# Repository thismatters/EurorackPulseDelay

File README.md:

# Pulse Delay

The circuit here is based on the [Yusynth Pulse Delay](https://yusynth.net/Modular/EN/PULSEDELAY/index.html) with minor tweaks to make it more Eurorack friendly. The changes I've made are thus:
* Selected resistors appropriate for +/-12V rails,
* Added polarity protection so that a backward power header doesn't fry anything (twin series schotty diodes: BAT54SL),
* Full surface mount design.

The Yusynth page is a treasure trove of information about this circuit that I am too amateur to claim as my own; please read that outstanding page before using this circuit. The page provides many details and other implementations of this circuit that you may find suitable.

The KiCAD project here uses the library/footprints [found in my companion repo](https://github.com/thismatters/EurorackKiCAD).

## Width

13hp on an Intellijel 1U rack.

## Inputs

Jack for gate/pulse input.

Knobs for:
* Pulse delay
* Pulse width

## Outputs

Jack for gate/pulse output.

LED to indicate output.

## Vendors

There are part numbers in the [BOM](pulse-delay.csv) for many of the parts (not for basic passives though) at the following vendors:

* [Mouser](https://www.mouser.com): Needs no introduction. Get your ICs from here (or [digikey](https://www.digikey.com)).
* [Tayda Electronics](https://www.taydaelectronics.com/): Good supplier for passive components; audio jacks, and potentiometers. Their audio jacks are slightly smaller than the thonkiconn from thonk.
* [Love My Switches](https://lovemyswitches.com/): Has [really good knobs](https://lovemyswitches.com/anodized-aluminum-knob-the-lo-fi-1-4-smooth-shaft-12-5mm-od/) to go on those potentiometers!
* [OSHPark](https://oshpark.com/): Fast and (relatively) cheap PCB manufacturer. Prototype run pending.

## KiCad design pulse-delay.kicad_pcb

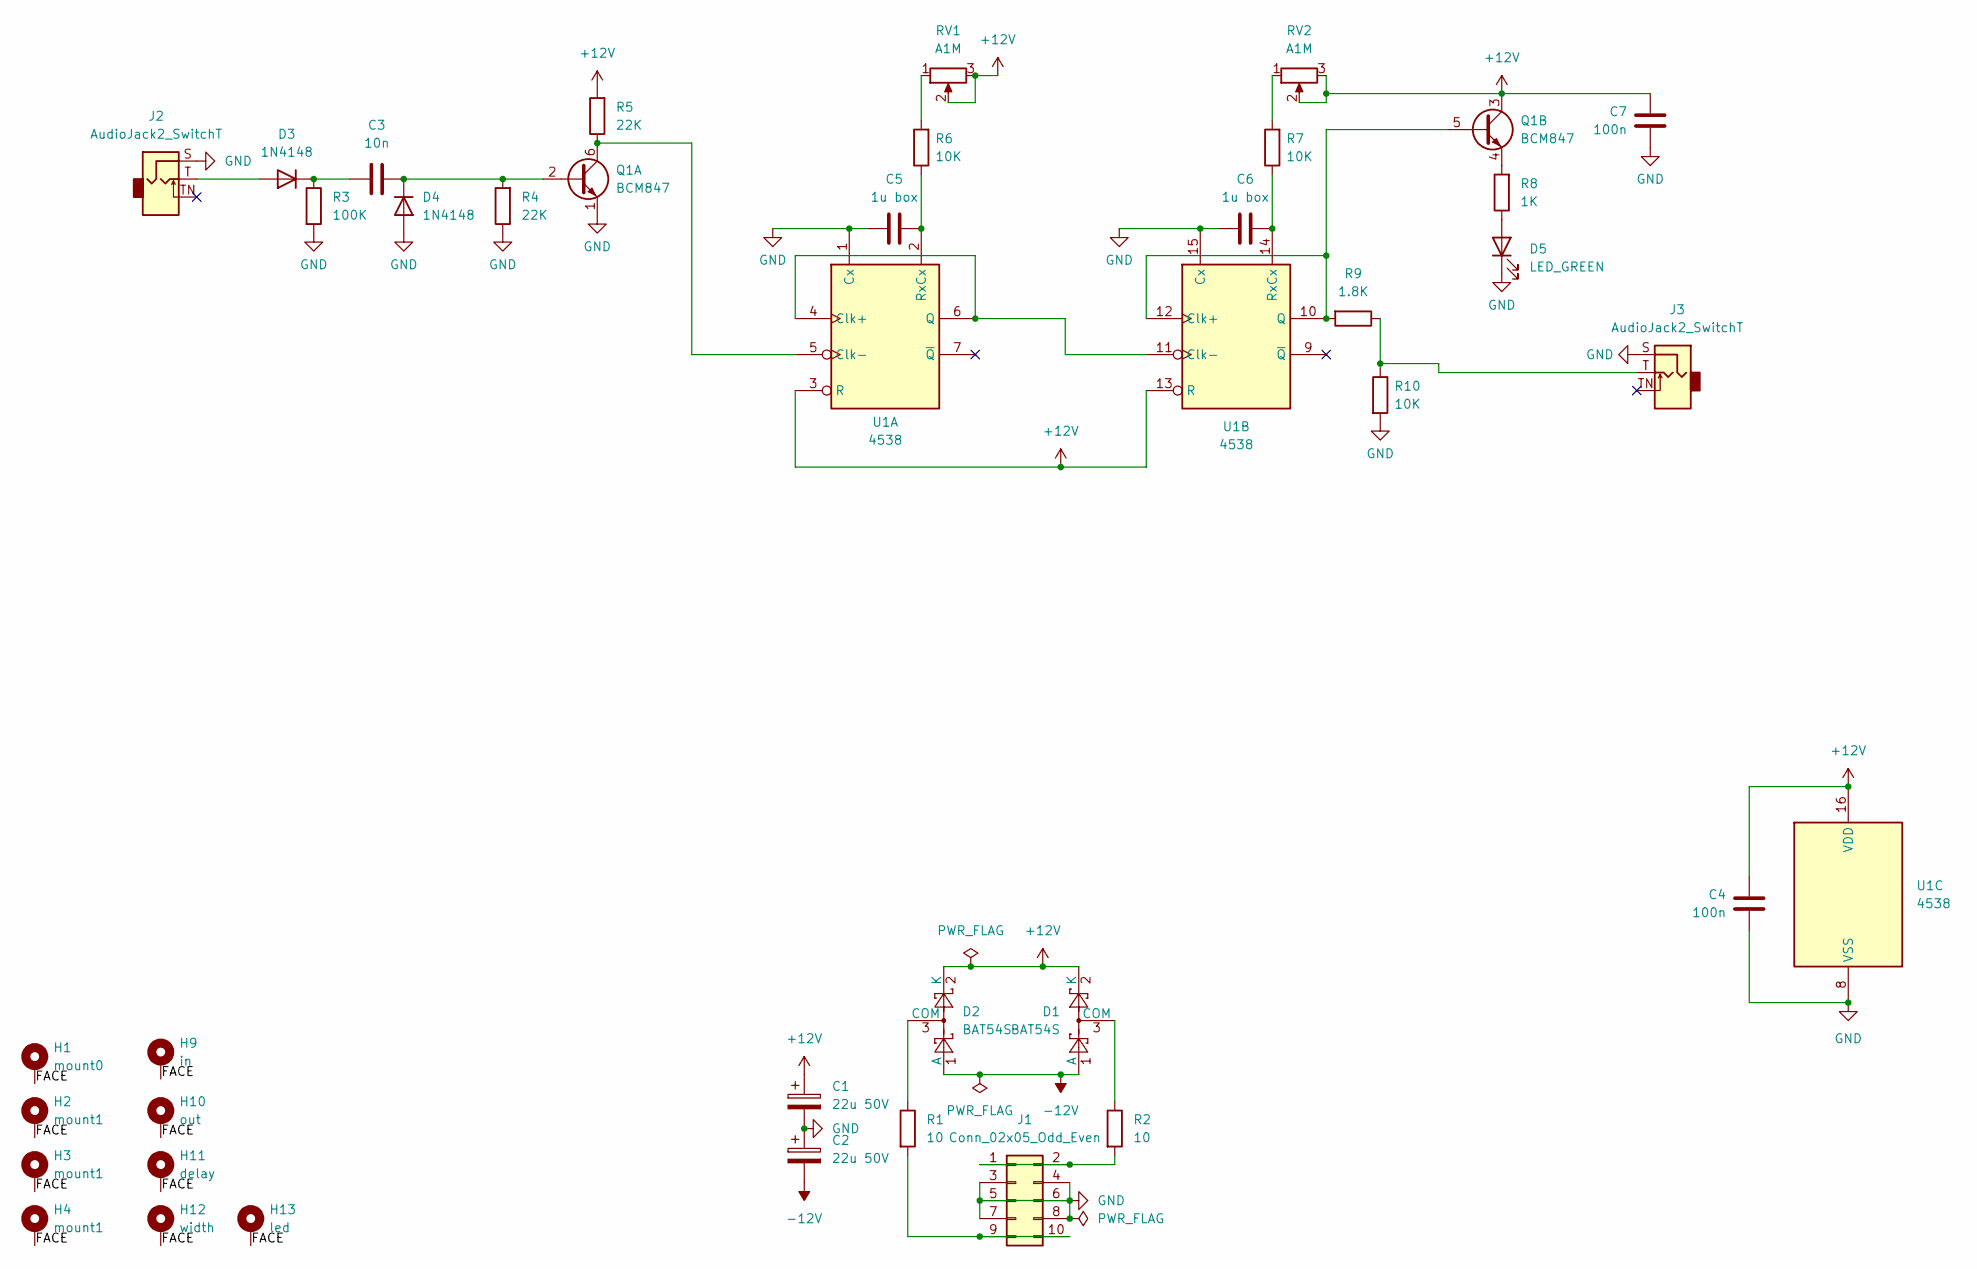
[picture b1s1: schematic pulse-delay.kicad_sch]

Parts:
C1, C2: 22u 50V; CP_Radial_D5.0mm_P2.50mm
C3: 10n; C_0805_2012Metric
C4, C7: 100n; C_0805_2012Metric
C5, C6: 1u box; C_Rect_L7.2mm_W5.5mm_P5.00mm_FKS2_FKP2_MKS2_MKP2
D1, D2: BAT54S; SOT-23; PartNum 863-BAT54SLT1G
D3, D4: 1N4148; D_SOD-323_HandSoldering
D5: LED_GREEN; LED_D3.0mm
H1: mount0; Mech-MountingHole
H2, H3, H4: mount1; Mech-MountingHole
H9: in; Mech-AudioJack-Hole-Input-Gate
H10: out; Mech-AudioJack-Hole-Output-Gate
H11: delay; Mech-Potentiometer-Hole_level_90deg
H12: width; Mech-Potentiometer-Hole_level_90deg
H13: led; Mech-LED-Hole-3mm-Bezel
J1: Conn_02x05_Odd_Even; PinHeader_2x05_P2.54mm_Vertical; PartNum A-2939
J2, J3: AudioJack2_SwitchT; AudioJack2_Tayda_A-2566; PartNum A-2566
Q1: BCM847; TSOP-6_1.65x3.05mm_P0.95mm; PartNum 771-BCM847DS135
R1, R2: 10; R_0805_2012Metric
R3: 100K; R_0805_2012Metric
R4, R5: 22K; R_0805_2012Metric
R6, R7, R10: 10K; R_0805_2012Metric
R8: 1K; R_0805_2012Metric
R9: 1.8K; R_0805_2012Metric
RV1, RV2: A1M; Potentiometer_RV16AF-41-15R1
U1: 4538; TSSOP-16_4.4x5mm_P0.65mm; PartNum 595-CD14538BPWR

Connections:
+12V: C1.1, C4.1, C7.1, D1.2 (K), D2.2 (K), Q1.3 (C2), R5.2, RV1.2, RV1.3, RV2.2, RV2.3, U1.3 (R), U1.13 (R), U1.16 (VDD)
-12V: C2.2, D1.1 (A), D2.1 (A)
/FACE: H1.1, H2.1, H3.1, H4.1, H9.1, H10.1, H11.1, H12.1, H13.1
GND: C1.2, C2.1, C4.2, C5.1, C6.1, C7.2, D4.2 (A), D5.1 (K), J1.3, J1.4, J1.5, J1.6, J1.7, J1.8, J2.S, J3.S, Q1.1 (E1), R3.2, R4.1, R10.2, U1.1 (Cx), U1.8 (VSS), U1.15 (Cx)
unnamed: D1.3 (COM), R2.1
unnamed: D2.3 (COM), R1.1
unnamed: D3.2 (A), J2.T
unnamed: C3.1, D3.1 (K), R3.1
unnamed: C3.2, D4.1 (K), Q1.2 (B1), R4.2
unnamed: D5.2 (A), R8.1
unnamed: J1.1, J1.2, R2.2
unnamed: J1.9, J1.10, R1.2
unnamed: J3.T, R9.1, R10.1
unnamed: Q1.6 (C1), R5.1, U1.5 (Clk-)
unnamed: Q1.5 (B2), R9.2, U1.10 (Q), U1.12 (Clk+)
unnamed: Q1.4 (E2), R8.2
unnamed: R6.2, RV1.1
unnamed: R7.2, RV2.1
unnamed: U1.4 (Clk+), U1.6 (Q), U1.11 (Clk-)
unnamed: C5.2, R6.1, U1.2 (RxCx)
unnamed: C6.2, R7.1, U1.14 (RxCx)

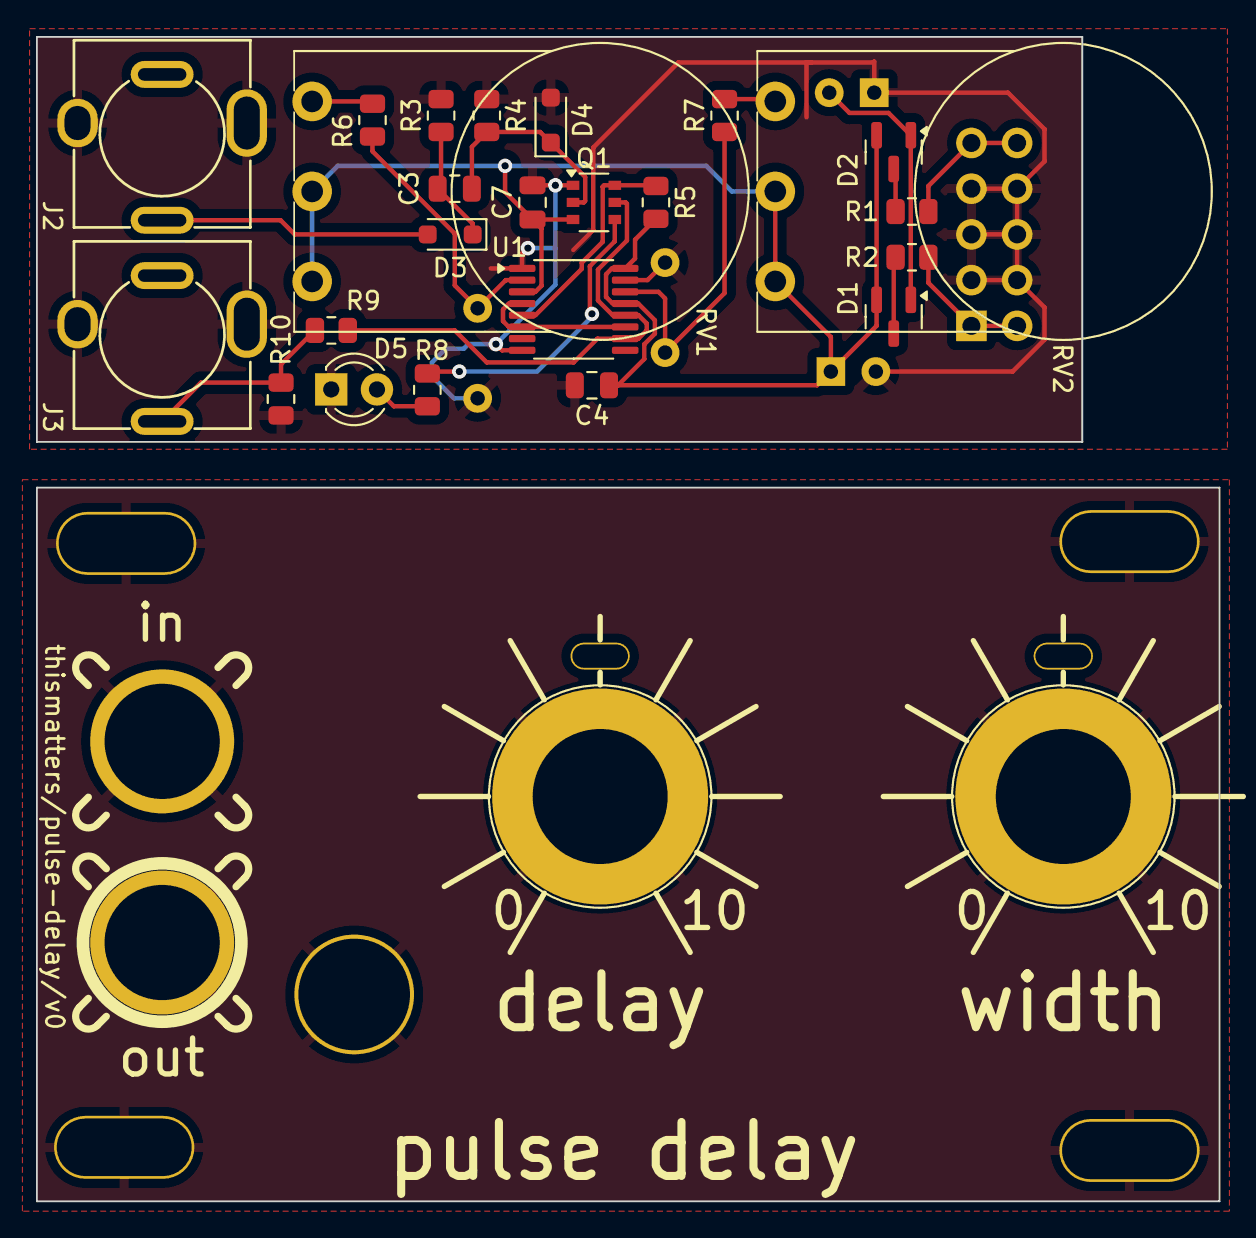
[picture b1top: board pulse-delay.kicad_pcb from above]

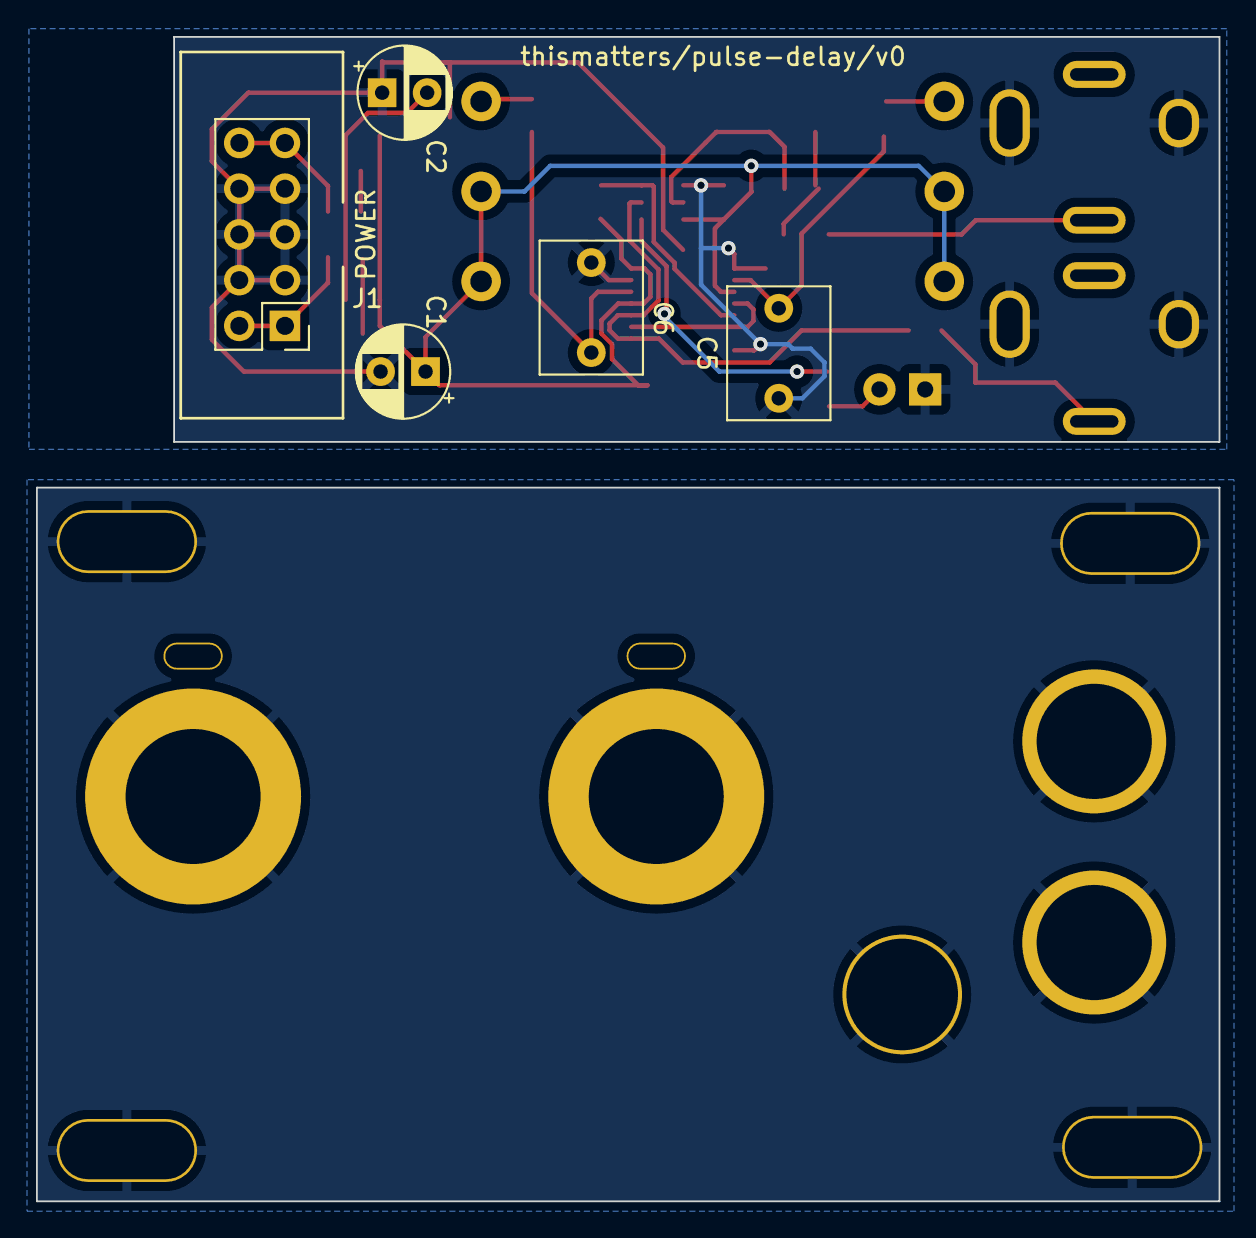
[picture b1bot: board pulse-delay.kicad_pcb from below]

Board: 2 copper layers, 65.7 x 64.7 mm, 38 parts (5 on the bottom side), 21 nets.

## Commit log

2025-04-05 pcb ready for v0
2025-04-08 update bom
